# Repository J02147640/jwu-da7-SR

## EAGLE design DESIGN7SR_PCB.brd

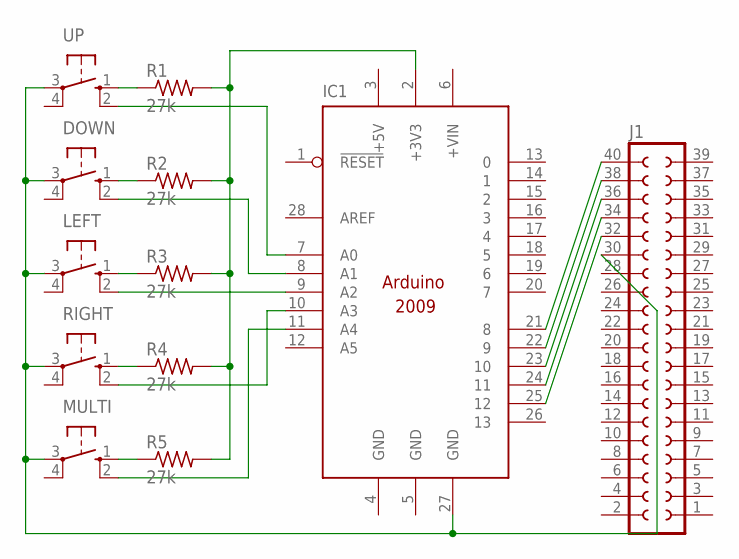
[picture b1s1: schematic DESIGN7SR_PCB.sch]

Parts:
DOWN: 10-XX; B3F-10XX
IC1: ARDUINO2009_10; ARDUINO2009
J1: SOCKET-40V; S40V
LEFT: 10-XX; B3F-10XX
MULTI: 10-XX; B3F-10XX
R1, R2, R3, R4, R5: 27k; 0204V
RIGHT: 10-XX; B3F-10XX
UP: 10-XX; B3F-10XX

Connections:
+5V: IC1.3 (+5V)
GND: IC1.4 (GND), IC1.5 (GND)
unnamed: IC1.21 (8), J1.40
unnamed: IC1.22 (9), J1.38
unnamed: IC1.23 (10), J1.36
unnamed: IC1.24 (11), J1.34
unnamed: IC1.25 (12), J1.32
unnamed: IC1.11 (A4), MULTI.2 (S1)
unnamed: DOWN.3, IC1.27 (GND), J1.30, LEFT.3, MULTI.3, RIGHT.3, UP.3
unnamed: IC1.10 (A3), RIGHT.2 (S1)
unnamed: R1.1, UP.1 (S)
unnamed: DOWN.1 (S), R2.1
unnamed: LEFT.1 (S), R3.1
unnamed: R4.1, RIGHT.1 (S)
unnamed: MULTI.1 (S), R5.1
unnamed: IC1.2 (+3V3), R1.2, R2.2, R3.2, R4.2, R5.2
unnamed: IC1.9 (A2), LEFT.2 (S1)
unnamed: DOWN.2 (S1), IC1.8 (A1)
unnamed: IC1.7 (A0), UP.2 (S1)

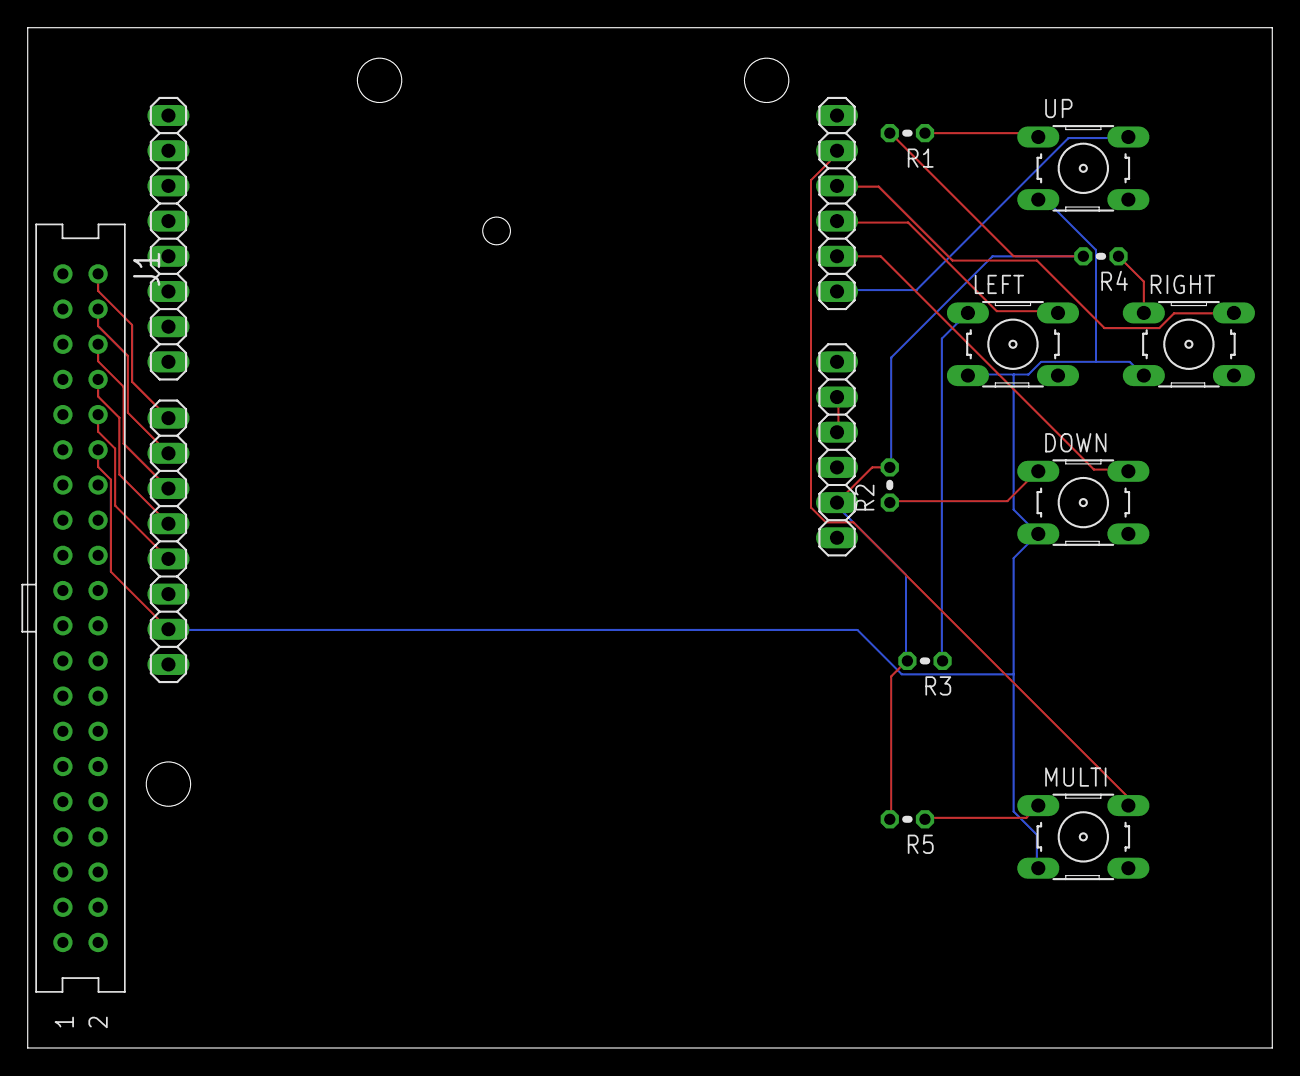
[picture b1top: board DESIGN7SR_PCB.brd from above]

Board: 2 copper layers, 89.8 x 73.7 mm, 12 parts (0 on the bottom side), 18 nets.
